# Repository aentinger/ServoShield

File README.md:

💾 Servo Shield
===============

# 📸 Image

# 📂 Description

The LXRobotics Servo Shield facilitates the control of up to 32 model making (RC) servos. The control of the servos is done over two special ICs of type PCA9685 which communicates via I2C-Interface with Arduino - for the control of 32 servos only two Arduino Pins are required. For the servo supply, a dedicated linear voltage regulator is built on the Servo Shield, whereat using jumper can be switched over between the voltage regulator of the Servo Shield and the Arduino's power supply. Alternatively, the Servo Shield can be also externally power supplied via plug connector. For the quick start, a finished Arduino Library with sample programs is available.

**Features**

* Control of up to 32 Model making (RC) Servos
* Separate linear voltage regulator 
* Different options for the power supply of servos: Arduino, Servo Shield, Extern
* Control via I2C – thre are only two Arduino-Pins required (SDA, SCL)
* I2C-Address using Jumper adjustable - up to 25 = 32 different addresses possible
* Stackable - multiple Servo Shields can be put on top of each other and controlled over only one Arduino (theoretically 32 Servo Shields are possible)
* I2C-PullUp-Resistor via jumper adjustable
* Status-LED for the visualization of the supply state of the Servo Shields
* Activation/Deactivation of all Servo outputs of PCA 9685 over digital outputs possible ( function via jumper connected/disconnected)
* Arduino Library available for control with example programs

# 🎥 [Video](images/servo_shield_demo.mp4)

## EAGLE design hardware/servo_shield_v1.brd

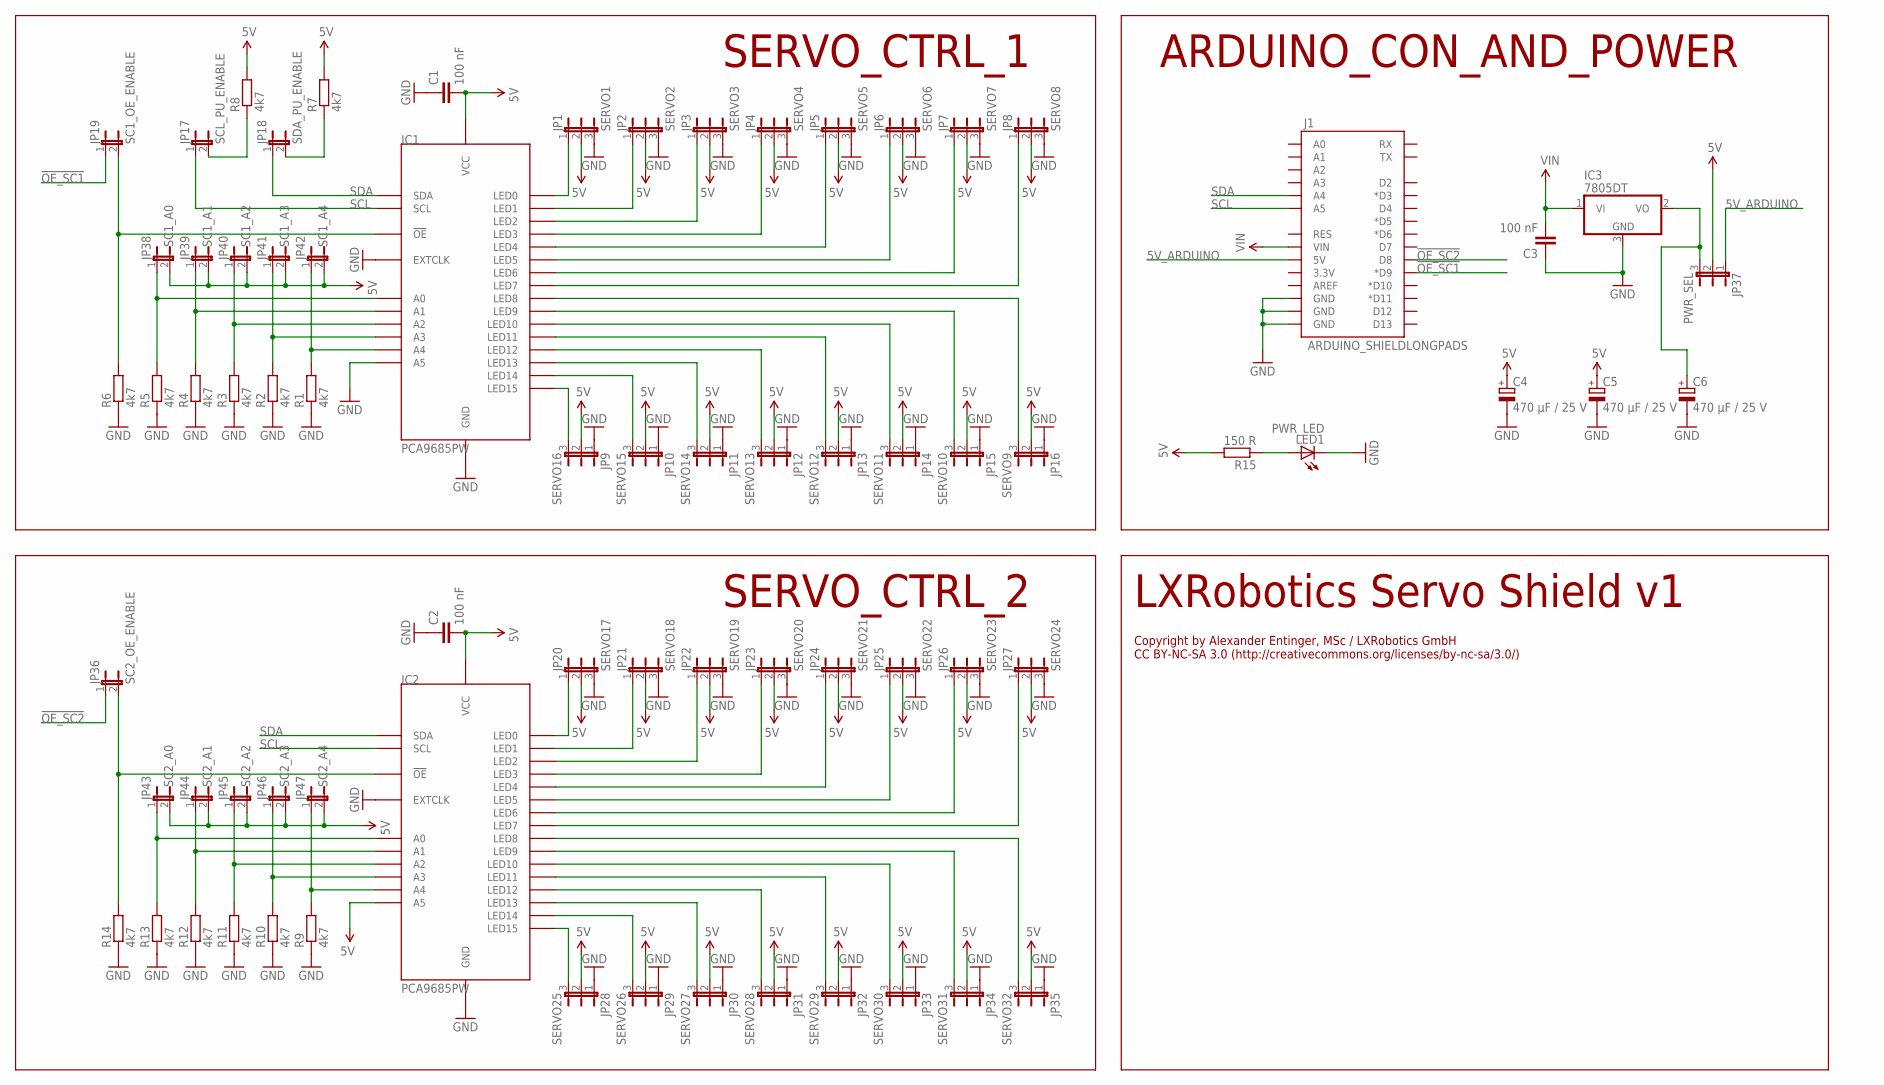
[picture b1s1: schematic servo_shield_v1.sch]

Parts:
C1, C2, C3: 100 nF; C0805K
C4, C5, C6: 470 µF / 25 V; E5-10,5
IC1, IC2: PCA9685PW; TSSOP28
IC3: 7805DT; TO252
J1: ARDUINO_SHIELDLONGPADS; DUEMILANOVE_SHIELD_LONGPADS
JP1: SERVO1; JP2
JP2: SERVO2; JP2
JP3: SERVO3; JP2
JP4: SERVO4; JP2
JP5: SERVO5; JP2
JP6: SERVO6; JP2
JP7: SERVO7; JP2
JP8: SERVO8; JP2
JP9: SERVO16; JP2
JP10: SERVO15; JP2
JP11: SERVO14; JP2
JP12: SERVO13; JP2
JP13: SERVO12; JP2
JP14: SERVO11; JP2
JP15: SERVO10; JP2
JP16: SERVO9; JP2
JP17: SCL_PU_ENABLE; JP1
JP18: SDA_PU_ENABLE; JP1
JP19: SC1_OE_ENABLE; JP1
JP20: SERVO17; JP2
JP21: SERVO18; JP2
JP22: SERVO19; JP2
JP23: SERVO20; JP2
JP24: SERVO21; JP2
JP25: SERVO22; JP2
JP26: SERVO23; JP2
JP27: SERVO24; JP2
JP28: SERVO25; JP2
JP29: SERVO26; JP2
JP30: SERVO27; JP2
JP31: SERVO28; JP2
JP32: SERVO29; JP2
JP33: SERVO30; JP2
JP34: SERVO31; JP2
JP35: SERVO32; JP2
JP36: SC2_OE_ENABLE; JP1
JP37: PWR_SEL; JP2
JP38: SC1_A0; JP1
JP39: SC1_A1; JP1
JP40: SC1_A2; JP1
JP41: SC1_A3; JP1
JP42: SC1_A4; JP1
JP43: SC2_A0; JP1
JP44: SC2_A1; JP1
JP45: SC2_A2; JP1
JP46: SC2_A3; JP1
JP47: SC2_A4; JP1
LED1: PWR_LED; CHIPLED_0805
R1, R2, R3, R4, R5, R6, R7, R8, R9, R10, R11, R12, R13, R14: 4k7; R0805W
R15: 150 R; R0805W

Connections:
5V: C1.2, C2.2, C4.+, C5.+, IC1.28 (VCC), IC2.24 (A5), IC2.28 (VCC), JP1.2, JP2.2, JP3.2, JP4.2, JP5.2, JP6.2, JP7.2, JP8.2, JP9.2, JP10.2, JP11.2, JP12.2, JP13.2, JP14.2, JP15.2, JP16.2, JP20.2, JP21.2, JP22.2, JP23.2, JP24.2, JP25.2, JP26.2, JP27.2, JP28.2, JP29.2, JP30.2, JP31.2, JP32.2, JP33.2, JP34.2, JP35.2, JP37.2, JP38.2, JP39.2, JP40.2, JP41.2, JP42.2, JP43.2, JP44.2, JP45.2, JP46.2, JP47.2, R7.2, R8.2, R15.2
5V_ARDUINO: J1.5V, JP37.1
!OE_SC1: J1.D9 (*D9), JP19.1
!OE_SC2: J1.D8, JP36.1
GND: C1.1, C2.1, C3.1, C4.-, C5.-, C6.-, IC1.14 (GND), IC1.24 (A5), IC1.25 (EXTCLK), IC2.14 (GND), IC2.25 (EXTCLK), IC3.3 (GND), J1.GND@0 (GND), J1.GND@1 (GND), J1.GND@2 (GND), JP1.3, JP2.3, JP3.3, JP4.3, JP5.3, JP6.3, JP7.3, JP8.3, JP9.1, JP10.1, JP11.1, JP12.1, JP13.1, JP14.1, JP15.1, JP16.1, JP20.3, JP21.3, JP22.3, JP23.3, JP24.3, JP25.3, JP26.3, JP27.3, JP28.1, JP29.1, JP30.1, JP31.1, JP32.1, JP33.1, JP34.1, JP35.1, LED1.C, R1.1, R2.1, R3.1, R4.1, R5.1, R6.1, R9.1, R10.1, R11.1, R12.1, R13.1, R14.1
unnamed: IC1.6 (LED0), JP1.1
unnamed: IC1.7 (LED1), JP2.1
unnamed: IC1.8 (LED2), JP3.1
unnamed: IC1.9 (LED3), JP4.1
unnamed: IC1.10 (LED4), JP5.1
unnamed: IC1.11 (LED5), JP6.1
unnamed: IC1.12 (LED6), JP7.1
unnamed: IC1.13 (LED7), JP8.1
unnamed: IC1.22 (LED15), JP9.3
unnamed: IC1.21 (LED14), JP10.3
unnamed: IC1.20 (LED13), JP11.3
unnamed: IC1.19 (LED12), JP12.3
unnamed: IC1.18 (LED11), JP13.3
unnamed: IC1.17 (LED10), JP14.3
unnamed: IC1.16 (LED9), JP15.3
unnamed: IC1.15 (LED8), JP16.3
unnamed: IC1.5 (A4), JP42.1, R1.2
unnamed: IC1.4 (A3), JP41.1, R2.2
unnamed: IC1.3 (A2), JP40.1, R3.2
unnamed: IC1.2 (A1), JP39.1, R4.2
unnamed: IC1.1 (A0), JP38.1, R5.2
unnamed: IC1.23 (!OE), JP19.2, R6.2
unnamed: C6.+, IC3.2 (VO), JP37.3
unnamed: IC2.6 (LED0), JP20.1
unnamed: IC2.7 (LED1), JP21.1
unnamed: JP17.2, R8.1
unnamed: JP18.2, R7.1
unnamed: IC2.8 (LED2), JP22.1
unnamed: IC2.9 (LED3), JP23.1
unnamed: IC2.10 (LED4), JP24.1
unnamed: IC2.11 (LED5), JP25.1
unnamed: IC2.12 (LED6), JP26.1
unnamed: IC2.13 (LED7), JP27.1
unnamed: IC2.22 (LED15), JP28.3
unnamed: IC2.21 (LED14), JP29.3
unnamed: IC2.20 (LED13), JP30.3
unnamed: IC2.19 (LED12), JP31.3
unnamed: IC2.18 (LED11), JP32.3
unnamed: IC2.17 (LED10), JP33.3
unnamed: IC2.16 (LED9), JP34.3
unnamed: IC2.15 (LED8), JP35.3
unnamed: IC2.5 (A4), JP47.1, R9.2
unnamed: IC2.4 (A3), JP46.1, R10.2
unnamed: IC2.3 (A2), JP45.1, R11.2
unnamed: IC2.2 (A1), JP44.1, R12.2
unnamed: IC2.1 (A0), JP43.1, R13.2
unnamed: IC2.23 (!OE), JP36.2, R14.2
unnamed: LED1.A, R15.1
SCL: IC1.26 (SCL), IC2.26 (SCL), J1.A5, JP17.1
SDA: IC1.27 (SDA), IC2.27 (SDA), J1.A4, JP18.1
VIN: C3.2, IC3.1 (VI), J1.VIN

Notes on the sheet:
SERVO_CTRL_1
SERVO_CTRL_2
ARDUINO_CON_AND_POWER
LXRobotics Servo Shield v1
Copyright by Alexander Entinger, MSc / LXRobotics GmbH CC BY-NC-SA 3.0 (http://creativecommons.org/licenses/by-nc-sa/3.0/)

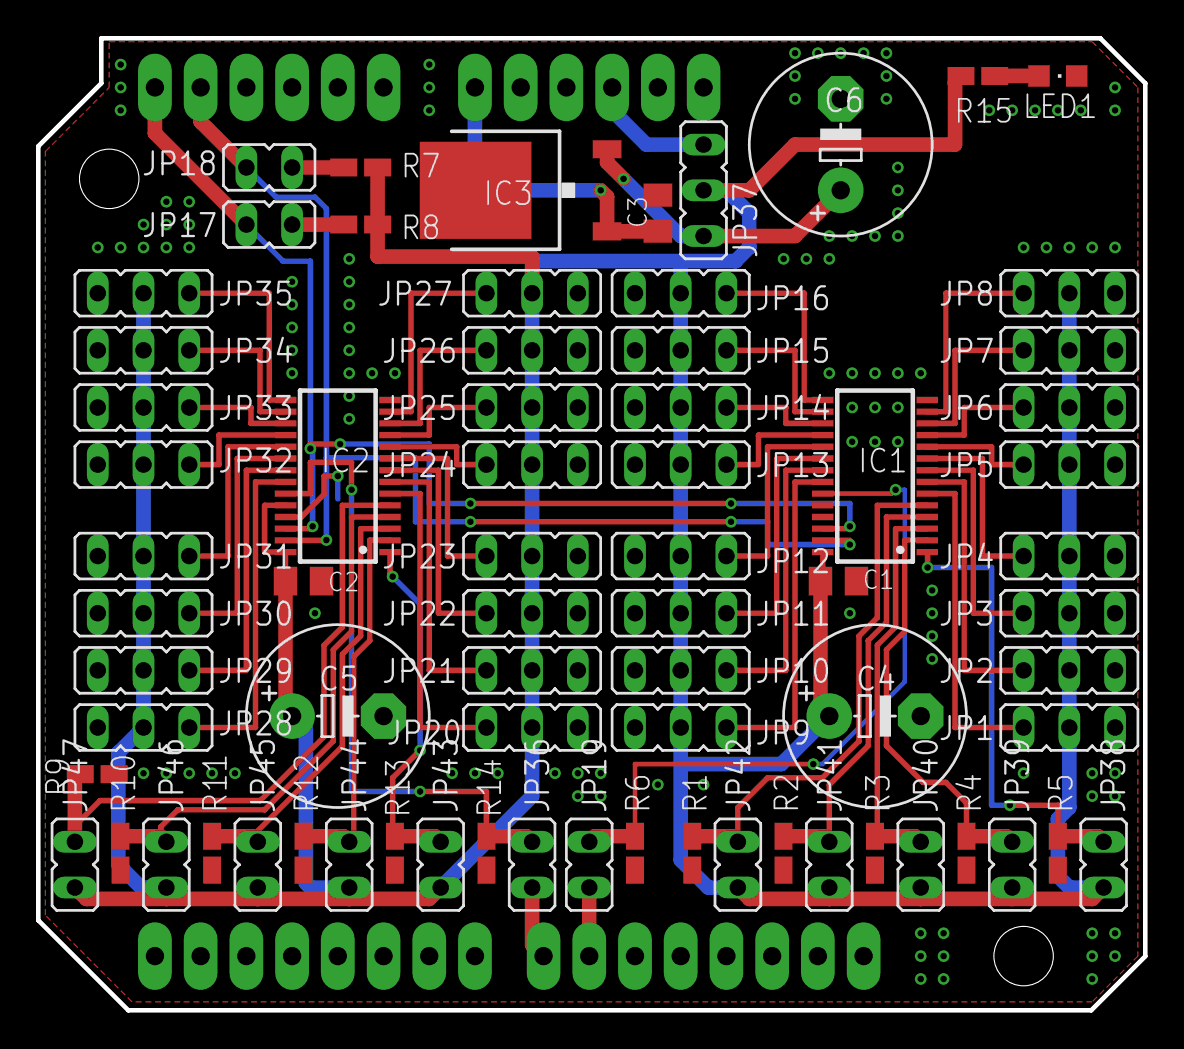
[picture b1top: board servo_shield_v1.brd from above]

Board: 2 copper layers, 61.5 x 54.0 mm, 73 parts (0 on the bottom side), 56 nets.

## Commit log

2015-01-11 initial checkin of servo shield software support pack
2017-06-27 Adding images + hardware
2025-03-26 Upload servo shield demo.
2025-03-26 Adding BOM.
2025-03-26 Pretty up README.
2025-03-26 Use relative link.

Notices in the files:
README.md:
License: CC BY-NC-SA 4.0
parts and their libraries:
SparkFun-Boards: Licensing: CC v3.0 Share-Alike You are welcome to use this library for commercial purposes.
